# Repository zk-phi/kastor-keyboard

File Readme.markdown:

# Kastor keyboard

※これは Kastor シリーズ試作第二版の紹介です。前作の組み立てガイドなどは [こちら](https://github.com/zk-phi/kastor-keyboard/tree/014ffdced01a2b5000a81938f7c5bd26ed5e1a9d) からどうぞ。

独自配列の 30% キーボードシリーズの試作第二版です。

特徴

- 内部の空洞を減らした独自の積層ケースで打鍵音＆デザイン性を向上
  - 打鍵音参考 https://twitter.com/zk_phi/status/1164212374150111237
- 最下段を親指で押しやすくした独自配列を採用

前作の独自配列と比較すると

- デザイン性のため、親指キーを手前にせり出させる仕様を廃止
- 代わりに最下段を外側に向かって 0.25u だけずらした新しい配列を採用、シンメトリーは諦め

となっています。

試作品のため、わかる人向けです

## 注意

設定ミスにより、上辺と底辺でネジ穴の位置が微妙にずれています。

これによって、一見上下対称に見える右手のプレートなども表裏を合わせないとネジが通りません。

組み立て時は注意してください。

## パーツ

※写真は４セット分です。。

- Kastor Rev.2 Kit
  - 基板２枚
  - 底板２枚
  - ボトムプレート２枚
  - ローワーミドルフレーム２枚
  - ミドルフレーム 上側・下側各２枚
  - ローワートッププレート２枚
  - トッププレート２枚
  - トップフレーム 薄・厚各２枚
- キースイッチ x36
- ダイオード 1N4148w x38
- TRRS ジャック MJ-4PP-9 x2
- 2 ピンタクトスイッチ x2
- コンスルー付き ProMicro x2 セット
- M2 ナット x20
- M2 ネジ 22mm x20 (プレートを全て使う場合)

## ケースのカスタマイズについて

- 底板を省略すると、一部の電子部品がむき出しになってしまう代わりにキーボードの高さを 2mm 抑えることができます
- トップフレームは 2mm 厚、3mm 厚のものが付属します。両方使って 5mm としてもいいですし、片方あるいは両方を省略することもできます

一部のプレートを省略する場合は、それに合わせてネジの長さも調節してください。

## 組み立て
### スイッチ以外の電子部品類の実装

1. リバーシブル基板なので、二枚の基板のうち片方を裏返しておく（右右や左左キーボードを作らないように！！）
2. ダイオードを半田付け x38 （基板の四角で囲まれている側 と、ダイオードの線の入っている側を合わせてください）
3. ダイオードを半田付けした面と同じ面から TRRS ジャック・リセットスイッチを刺して、半田付け x 各 2

### Pro Micro の実装

前作同様、 Pro Micro の実装向きが特殊なので注意してください。

1. 基板を裏返して、スイッチを実装した面が下に来るようにする
2. 基板にコンスルーを差し込む x4 （向きは Helix のビルドガイドなど参照。半田付けは不要）
3. 基板上の「TX」の目印に合わせて、コンスルーに ProMicro を載せる（左右のキーボードで ProMicro の裏表が逆になっていれば ok … 左手は ProMicro の部品面を２枚の基板で挟み込むように、右手は部品面がむき出しになるはず）
4. ProMicro とコンスルーの間だけを半田付け
5. ファームを焼いて動作確認

サンプルのファームウェアは https://github.com/zk-phi/qmk_firmware に kastor という名前で入っています。

: make kastor/rev2:phi:avrdude

ケーブル類を接続した状態でスイッチを取り付ける穴をピンセットなどで直接短絡させ、無事キー入力ができれば ok です。

### スイッチの実装

Pro Micro を外し、スイッチを実装します。まずはトッププレート・ローワートッププレートの向きを合わせます。紛らわしいので注意してください。

1. 基板を裏返して、上の手順で部品を実装した面が下側に来るようにする
2. TRRS ジャックやリセットスイッチの足が飛び出しているところにちょうど穴がくるようにローワートッププレートを重ねる
3. ローワートッププレートとネジ穴がぴったり合うようにトッププレートを重ねる

プレートの正しい向きがわかったら、スイッチを取り付けてゆきます。

1. トッププレート側から２枚を貫通するようにスイッチをセット
2. スイッチをプレートごと基板に挿入
3. Pro Micro のくる位置にあるスイッチだけは足をカット

スイッチを半田付けしてしまうと、半田をはがさない限りプレートの向きを直すことができなくなります。念のため再度向きを確認した上、半田付けしましょう。

### ケースを組み立てる

下から

- 底板
- ボトムプレート
- ローワーミドルフレーム
- ミドルフレーム 上側・下側
- 実装済みの基板＆トッププレート
- 好みの枚数のトップフレーム

をこの順に重ね、ネジで貫通・ナットで留めます。ミドルフレームの上側を除く全てのパーツで左右の別・向きがあります。ネジ穴がぴったり重なっていて、部品に干渉していなければ正しく積めています。

仕上げにゴム足を貼り付ければ完成です。

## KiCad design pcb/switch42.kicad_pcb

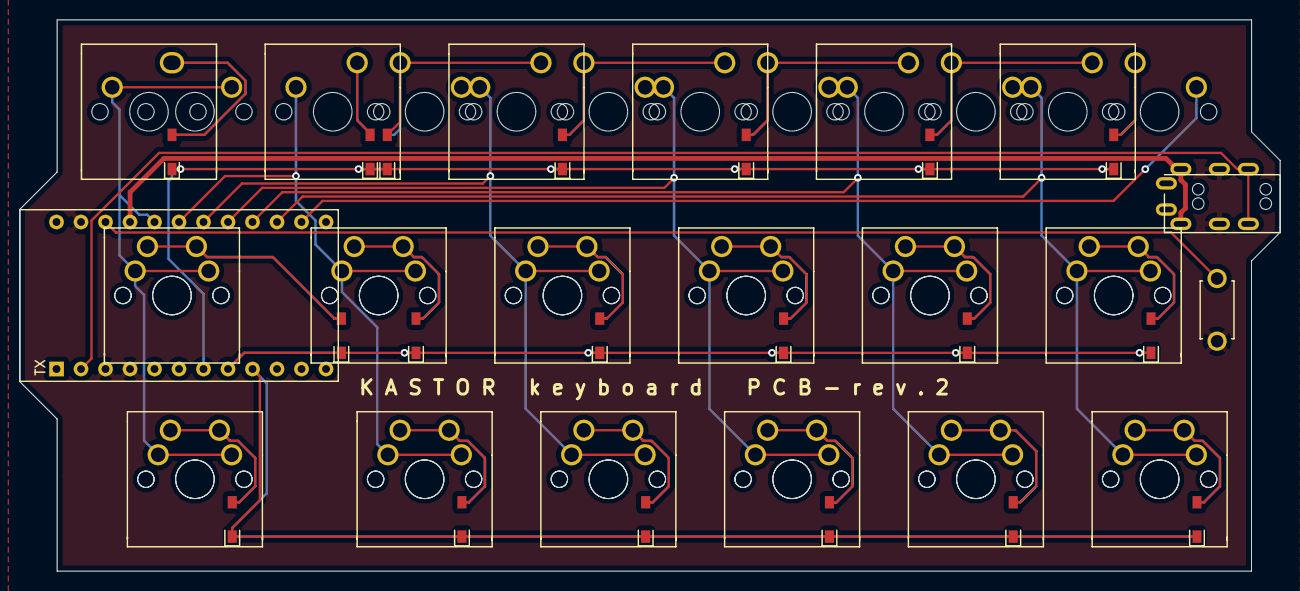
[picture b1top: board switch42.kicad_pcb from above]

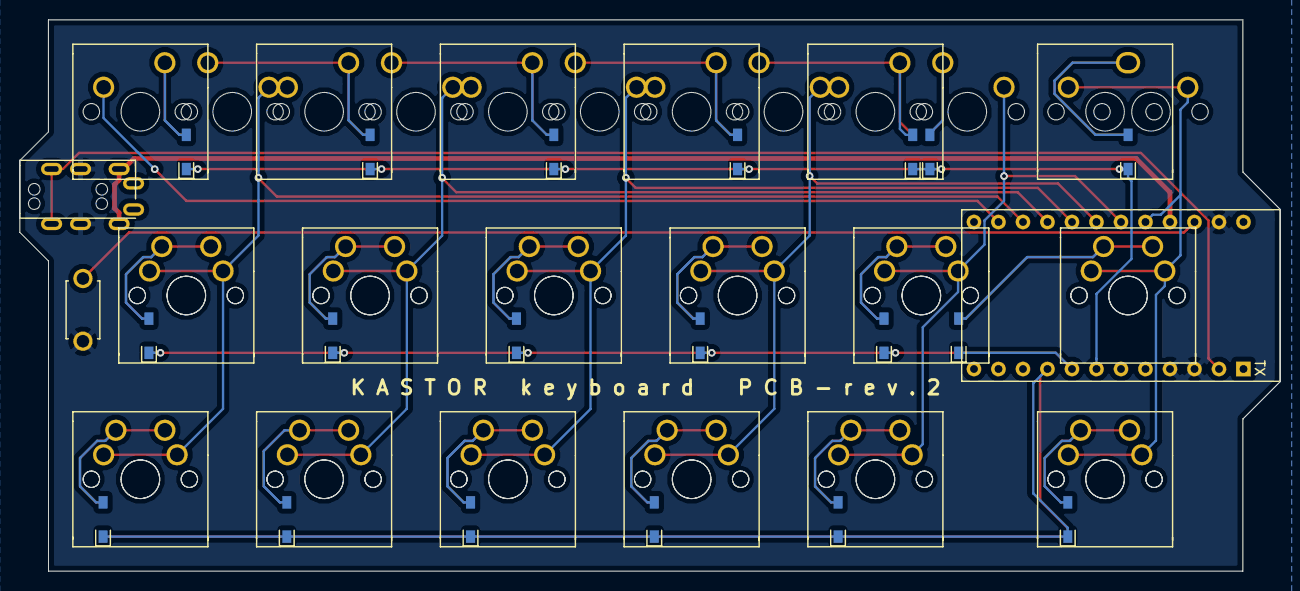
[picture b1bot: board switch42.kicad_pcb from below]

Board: 2 copper layers, 130.7 x 57.1 mm, 59 parts (21 on the bottom side), 33 nets.

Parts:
D1, D2, D3, D4, D5, D6, D7, D8, D9, D10, D11, D12, D13, D14, D15, D16, D17, D18, D19: D; D_SMD-reversible
J1, J2: MJ-4PP-9; MJ-4PP-9-irreversible
SW1: SW_PUSH; ResetSW-reversible
SW2, SW5, SW6, SW7, SW8, SW9, SW10, SW11, SW12, SW13, SW14, SW15, SW16, SW17, SW18, SW19, SW20, SW24, SW25, SW26, SW27, SW28, SW29, SW30, SW31, SW32, SW33, SW34, SW35, SW36, SW37: SW_PUSH; MX_1.00u-irreversible
SW3, SW21: SW_PUSH; MX_1.25u-irreversible
SW4, SW22, SW23: SW_PUSH; MX_1.50u-irreversible
U1: ProMicro; ProMicro_Reversed_Conthrough-single-reversible

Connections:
GND: J1.C, J2.C, SW1.2, U1.3, U1.4, U1.23
unnamed: D1.2, SW2.2, SW23.2
unnamed: D2.2, SW3.2, SW21.2
unnamed: D3.2, SW4.2, SW22.2
unnamed: D4.2, SW5.2
unnamed: D5.2, SW6.2, SW24.2
unnamed: D6.2, SW7.2, SW25.2
unnamed: D7.2, SW8.2, SW26.2
unnamed: D8.2, SW9.2, SW27.2
unnamed: D9.2, SW10.2, SW28.2
unnamed: D10.2, SW11.2, SW29.2
unnamed: D11.2, SW12.2, SW30.2
unnamed: D12.2, SW13.2, SW31.2
unnamed: D13.2, SW14.2, SW32.2
unnamed: D14.2, SW15.2, SW33.2
unnamed: D15.2, SW16.2, SW34.2
unnamed: D16.2, SW17.2, SW35.2
unnamed: D17.2, SW18.2, SW36.2
unnamed: D18.2, SW19.2, SW37.2
unnamed: D19.2, SW20.2
VCC: J1.D, J2.D, U1.21
col0: SW2.1, SW3.1, SW4.1, SW21.1, SW22.1, SW23.1, U1.20
col1: SW5.1, SW6.1, SW7.1, SW24.1, SW25.1, U1.19
col2: SW8.1, SW9.1, SW10.1, SW26.1, SW27.1, SW28.1, U1.18
col3: SW11.1, SW12.1, SW13.1, SW29.1, SW30.1, SW31.1, U1.17
col4: SW14.1, SW15.1, SW16.1, SW32.1, SW33.1, SW34.1, U1.16
col5: SW17.1, SW18.1, SW19.1, SW35.1, SW36.1, SW37.1, U1.15
col6: SW20.1, U1.14
data: J1.B, J2.B, U1.2
reset: SW1.1, U1.22
row0: D1.1, D4.1, D7.1, D10.1, D13.1, D16.1, D19.1, U1.7
row1: D2.1, D5.1, D8.1, D11.1, D14.1, D17.1, U1.8
row2: D3.1, D6.1, D9.1, D12.1, D15.1, D18.1, U1.9

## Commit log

2019-06-21 rev1
2019-06-21 Update footprints
2019-06-21 Update footprint
2019-07-02 Add Readme
2019-07-14 Add .gitignore
2019-08-11 Redraw schema and update pcb layout
2019-08-12 Add case model and remove old plate datas
2019-08-12 Tweak case kadomaru
2019-08-12 Complate wiring
2019-08-13 Add keyboard name silk to the pcb
2019-08-13 Reduce PCB thickness to 1.2mm
2019-08-13 Adjust diode positions
2019-08-13 Widen reset SW hole for leads
2019-08-13 Update PCB thickness
2019-08-13 Fix invalid slops for the topframe
2019-08-14 Tweak plate thickness
2021-06-30 Add preview.scad
